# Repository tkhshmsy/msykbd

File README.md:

# msykbd

tkhshmsy's original keyboard which contains pcb, chassis, and firmware

## why build this?

I have been using [Logitech G13](https://support.logitech.com/en_us/product/g13-advanced-gameboard) which is very good and my favorite one.

With long use, it became not to working properly...
So, I want NEW one, but, unfortunately, G13 was already discontinued production.

I decided to make it myself.

## product

- Left-hand Gaming Keypad
  - 35 Keys
  - AnalogStick (work as keys, not pointing device)

- Separate Ortholinear Keyboard
  - US 70 keys

## PCB

- designed with Kicad v5

### parts

- promicro (ATMega32U4@16MHz)
- OLED (128x32 with SSD1306)
- mechanical key switches
  - cherryMX or Kailh Lowprofile
- TRRS plug
  
## Firmware

- build with platformio
  - framework : arduino

### required libraries

- ID 891
  - Keyboard
- ID 13
  - Adafruit GFX
- ID 135
  - Adafruit SSD1306

## Chassis

- designed with Fusion360
  - export DXF and convert into Adobe Illustrator
- for LaserCutter 'trotec Speedy 300'
  - worked at [FabLab Setagaya at IID](http://fablabsetagaya.com/)

## Author

- tkhshmsy@gmail.com

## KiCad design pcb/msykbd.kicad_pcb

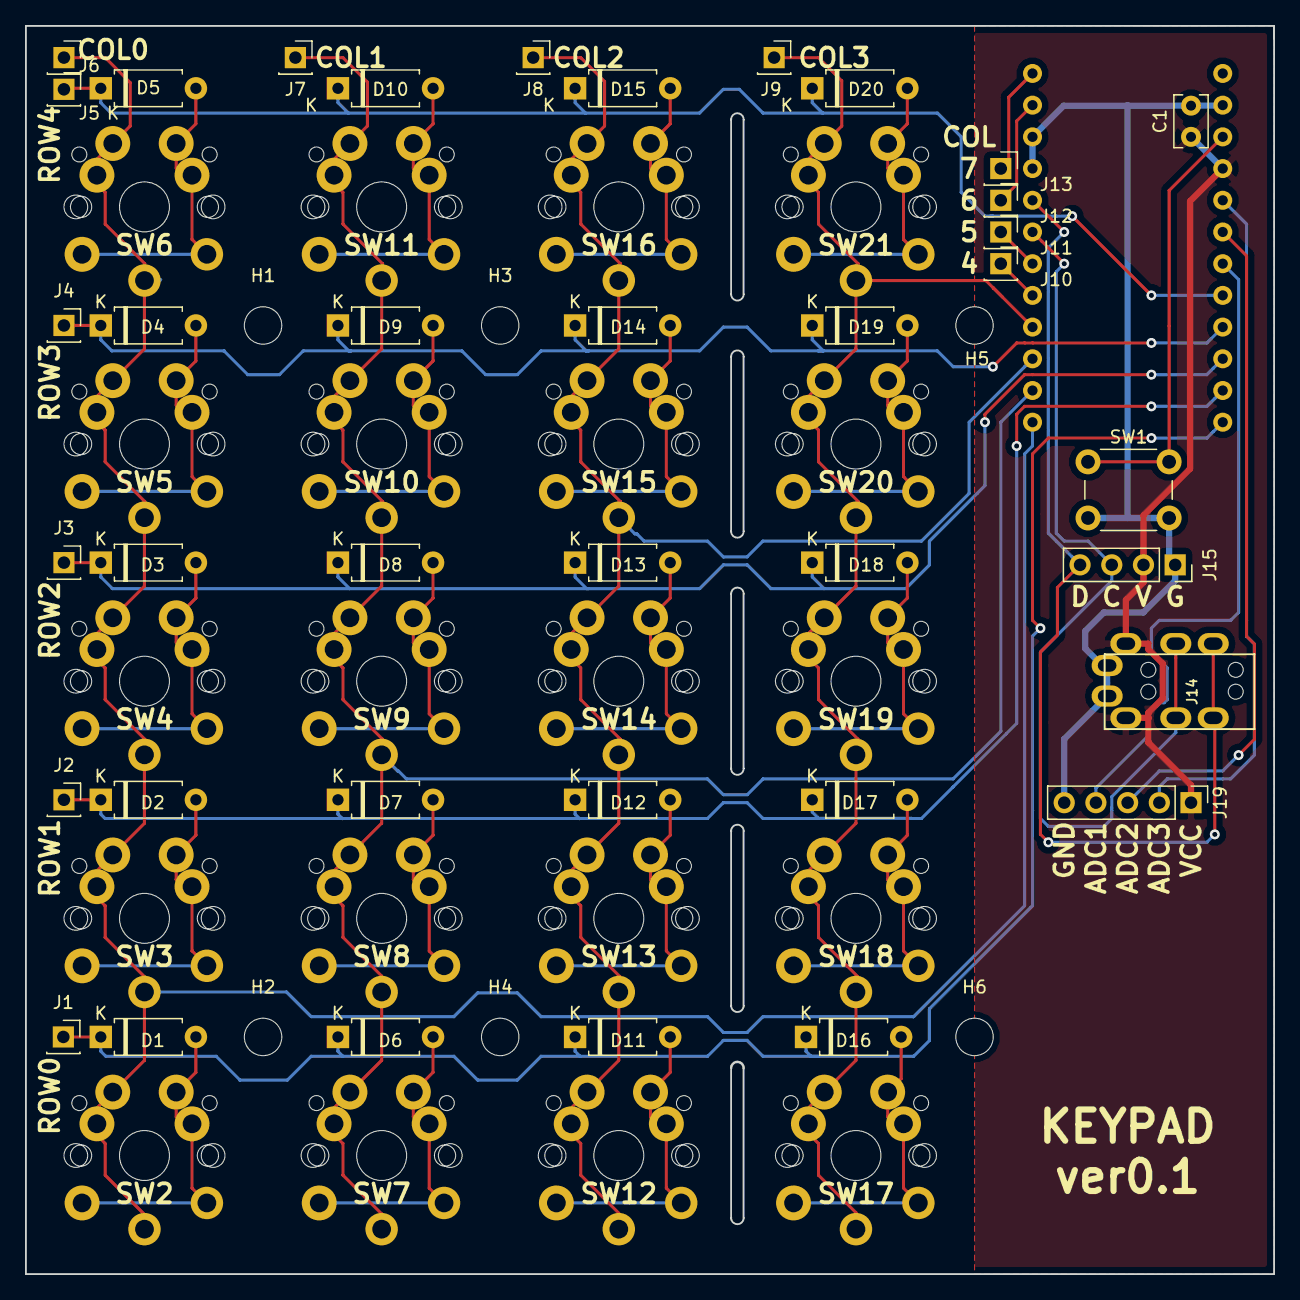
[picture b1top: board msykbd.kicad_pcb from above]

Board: 2 copper layers, 99.9 x 99.9 mm, 65 parts (0 on the bottom side), 41 nets.

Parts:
C1: C_Small; C_Rect_L4.0mm_W2.5mm_P2.50mm
D1, D2, D3, D4, D5, D6, D7, D8, D9, D10, D11, D12, D13, D14, D15, D16, D17, D18, D19, D20: D; D_A-405_P7.62mm_Horizontal
H1, H2, H3, H4, H5, H6: MountingHole; MountingHole_3mm
J1, J2, J3, J4, J5, J6, J7, J8, J9, J10, J11, J12, J13: Conn_01x01; PinSocket_1x01_P2.54mm_Vertical
J14: MJ-4PP-9; MJ-4PP-9_rev2
J15: Conn_01x04; PinSocket_1x04_P2.54mm_Vertical
J19: Conn_01x05; PinHeader_1x05_P2.54mm_Vertical
SW1: SW_Push; SW_PUSH_6mm
SW2, SW3, SW4, SW5, SW6, SW7, SW8, SW9, SW10, SW11, SW12, SW13, SW14, SW15, SW16, SW17, SW18, SW19, SW20, SW21: SW_Push; MX_PG1350-Under_FLIP_HOLES_
U1: ProMicro; ProMicro_rev

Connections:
+5V: C1.1, J14.D, J15.2, J19.1, U1.21
/ADC1: J19.4, U1.18
/ADC2: J19.3, U1.19
/ADC3: J19.2, U1.20
/COL0: J6.1, SW2.1, SW3.1, SW4.1, SW5.1, SW6.1, U1.12
/COL1: J7.1, SW7.1, SW8.1, SW9.1, SW10.1, SW11.1, U1.11
/COL2: J8.1, SW12.1, SW13.1, SW14.1, SW15.1, SW16.1, U1.10
/COL3: J9.1, SW17.1, SW18.1, SW19.1, SW20.1, SW21.1, U1.9
/COL4: J10.1, U1.8
/COL5: J11.1, U1.7
/COL6: J12.1, U1.2
/COL7: J13.1, U1.1
/ROW0: D1.1, D6.1, D11.1, D16.1, J1.1, U1.13
/ROW1: D2.1, D7.1, D12.1, D17.1, J2.1, U1.14
/ROW2: D3.1, D8.1, D13.1, D18.1, J3.1, U1.15
/ROW3: D4.1, D9.1, D14.1, D19.1, J4.1, U1.16
/ROW4: D5.1, D10.1, D15.1, D20.1, J5.1, U1.17
/SCL: J14.C, J15.3, U1.6
/SDA: J14.B, J15.4, U1.5
/nRST: SW1.1, U1.22
GND: C1.2, J14.A, J15.1, J19.5, SW1.2, U1.3, U1.4, U1.23
unnamed: D1.2, SW2.2
unnamed: D2.2, SW3.2
unnamed: D3.2, SW4.2
unnamed: D4.2, SW5.2
unnamed: D5.2, SW6.2
unnamed: D6.2, SW7.2
unnamed: D7.2, SW8.2
unnamed: D8.2, SW9.2
unnamed: D9.2, SW10.2
unnamed: D10.2, SW11.2
unnamed: D11.2, SW12.2
unnamed: D12.2, SW13.2
unnamed: D13.2, SW14.2
unnamed: D14.2, SW15.2
unnamed: D15.2, SW16.2
unnamed: D16.2, SW17.2
unnamed: D17.2, SW18.2
unnamed: D18.2, SW19.2
unnamed: D19.2, SW20.2
unnamed: D20.2, SW21.2

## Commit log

2019-04-04 ver 0.1
